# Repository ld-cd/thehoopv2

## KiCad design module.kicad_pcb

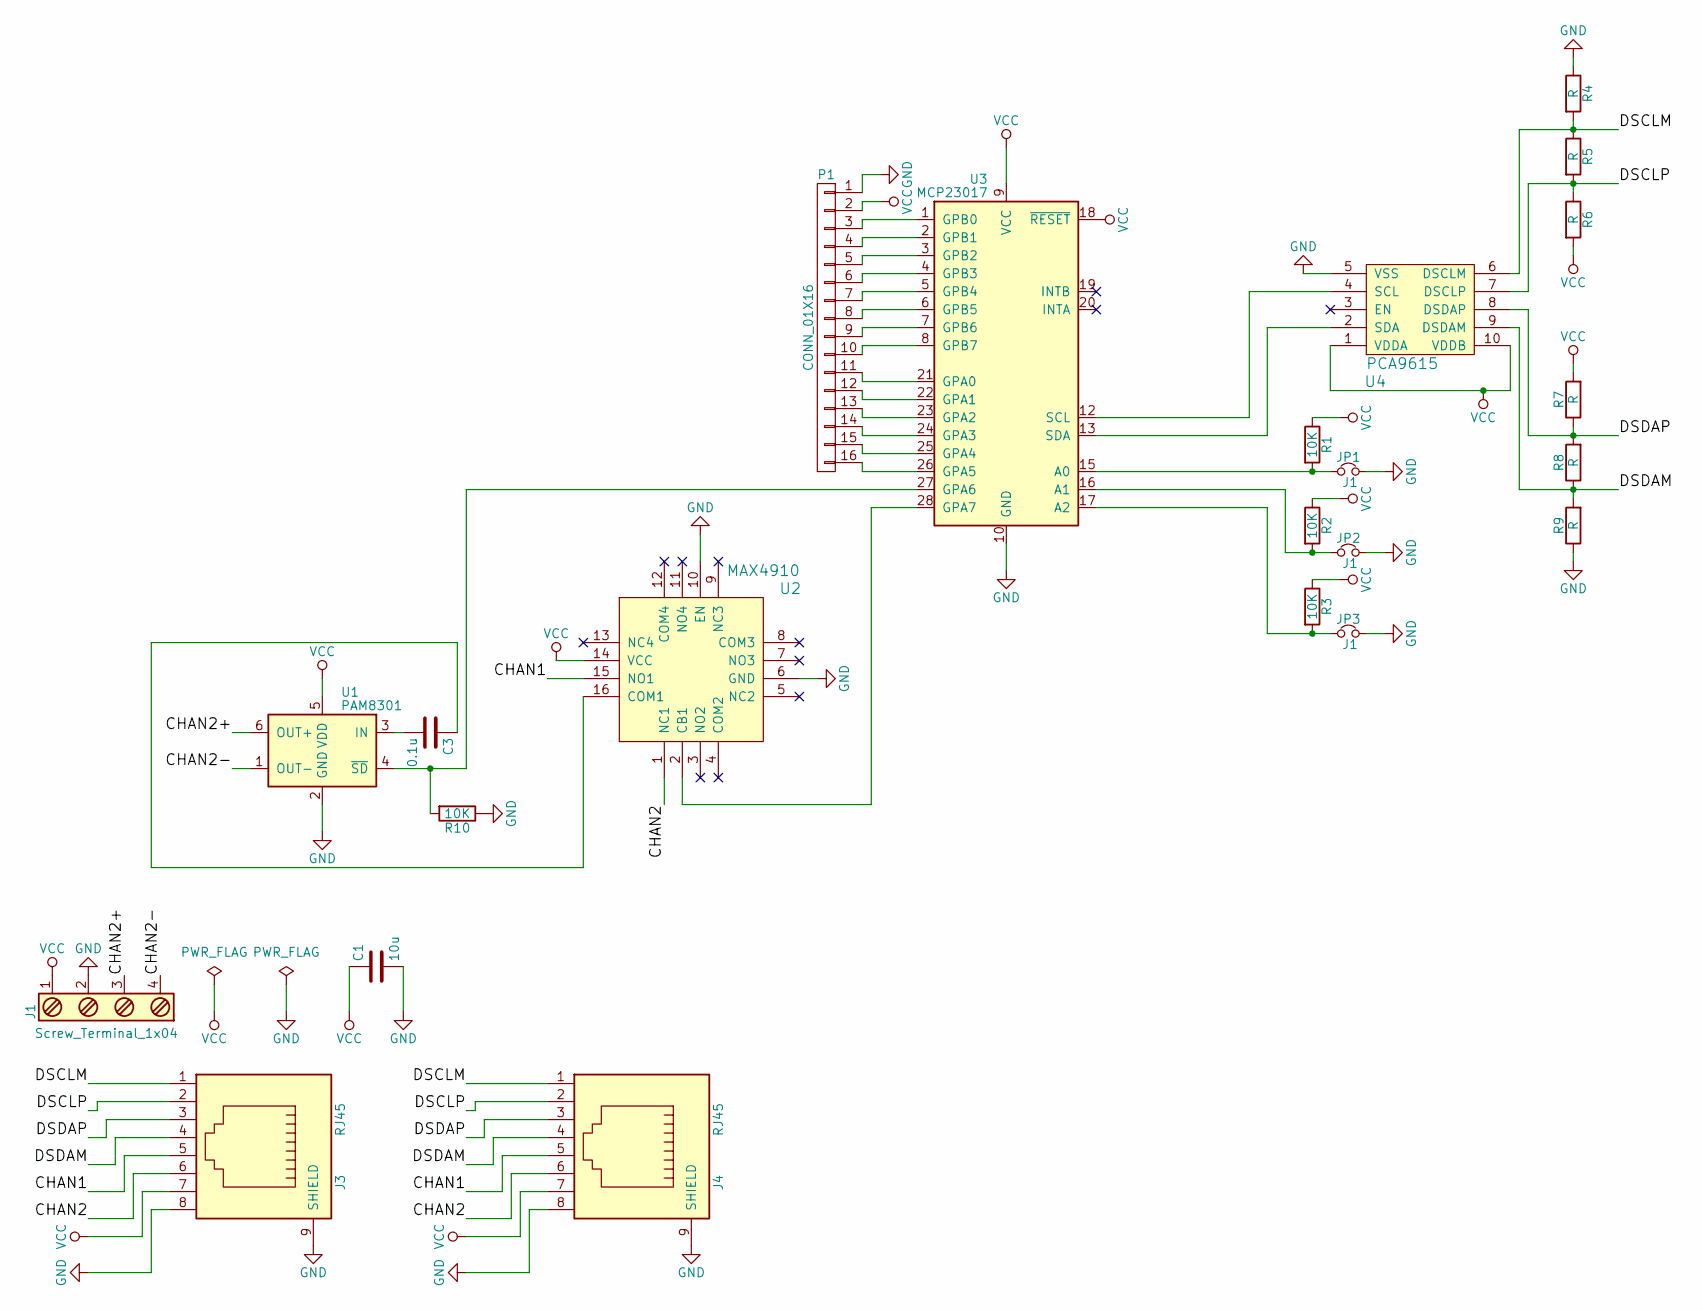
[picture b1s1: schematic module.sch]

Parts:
C1: 10u; C_0603
C3: 0.1u; C_0603
J1: Screw_Terminal_1x04; TerminalBlock_Pheonix_MKDS1.5-4pol
J3, J4: RJ45; rj45-8z4
JP1, JP2, JP3: J1; R_0603
P1: CONN_01X16; IDC_Header_Straight_16pins
R1, R2, R3, R10: 10K; R_0603
R4, R5, R6, R7, R8, R9: R; R_0603
U1: PAM8301; SOT-23-6
U2: MAX4910; QFN-16-1EP_3x3mm_Pitch0.5mm
U3: MCP23017; SSOP-28_5.3x10.2mm_Pitch0.65mm
U4: PCA9615; TSSOP-10_3x3mm_Pitch0.5mm

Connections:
/CHAN1: J3.5, J4.5, U2.15 (NO1)
/CHAN2: J3.6, J4.6, U2.1 (NC1)
/CHAN2+: J1.3, U1.6 (OUT+)
/CHAN2-: J1.4, U1.1 (OUT-)
/DSCLM: J3.1, J4.1, R4.2, R5.1, U4.6 (DSCLM)
/DSCLP: J3.2, J4.2, R5.2, R6.1, U4.7 (DSCLP)
/DSDAM: J3.4, J4.4, R8.1, R9.2, U4.9 (DSDAM)
/DSDAP: J3.3, J4.3, R7.1, R8.2, U4.8 (DSDAP)
GND: C1.2, J1.2, J3.8, J3.9 (SHIELD), J4.8, J4.9 (SHIELD), JP1.2, JP2.2, JP3.2, P1.1, R4.1, R9.1, R10.1, U1.2 (GND), U2.6 (GND), U2.10 (EN), U3.10 (GND), U4.5 (VSS)
unnamed: C3.1, U2.16 (COM1)
unnamed: C3.2, U1.3 (IN)
unnamed: JP1.1, R1.2, U3.15 (A0)
unnamed: JP2.1, R2.2, U3.16 (A1)
unnamed: JP3.1, R3.2, U3.17 (A2)
unnamed: P1.3, U3.1 (GPB0)
unnamed: P1.4, U3.2 (GPB1)
unnamed: P1.5, U3.3 (GPB2)
unnamed: P1.6, U3.4 (GPB3)
unnamed: P1.7, U3.5 (GPB4)
unnamed: P1.8, U3.6 (GPB5)
unnamed: P1.9, U3.7 (GPB6)
unnamed: P1.10, U3.8 (GPB7)
unnamed: P1.11, U3.21 (GPA0)
unnamed: P1.12, U3.22 (GPA1)
unnamed: P1.13, U3.23 (GPA2)
unnamed: P1.14, U3.24 (GPA3)
unnamed: P1.15, U3.25 (GPA4)
unnamed: P1.16, U3.26 (GPA5)
unnamed: R10.2, U1.4 (~SD), U3.27 (GPA6)
unnamed: U2.2 (CB1), U3.28 (GPA7)
unnamed: U3.12 (SCL), U4.4 (SCL)
unnamed: U3.13 (SDA), U4.2 (SDA)
VCC: C1.1, J1.1, J3.7, J4.7, P1.2, R1.1, R2.1, R3.1, R6.2, R7.2, U1.5 (VDD), U2.14 (VCC), U3.9 (VCC), U3.18 (~RESET), U4.1 (VDDA), U4.10 (VDDB)

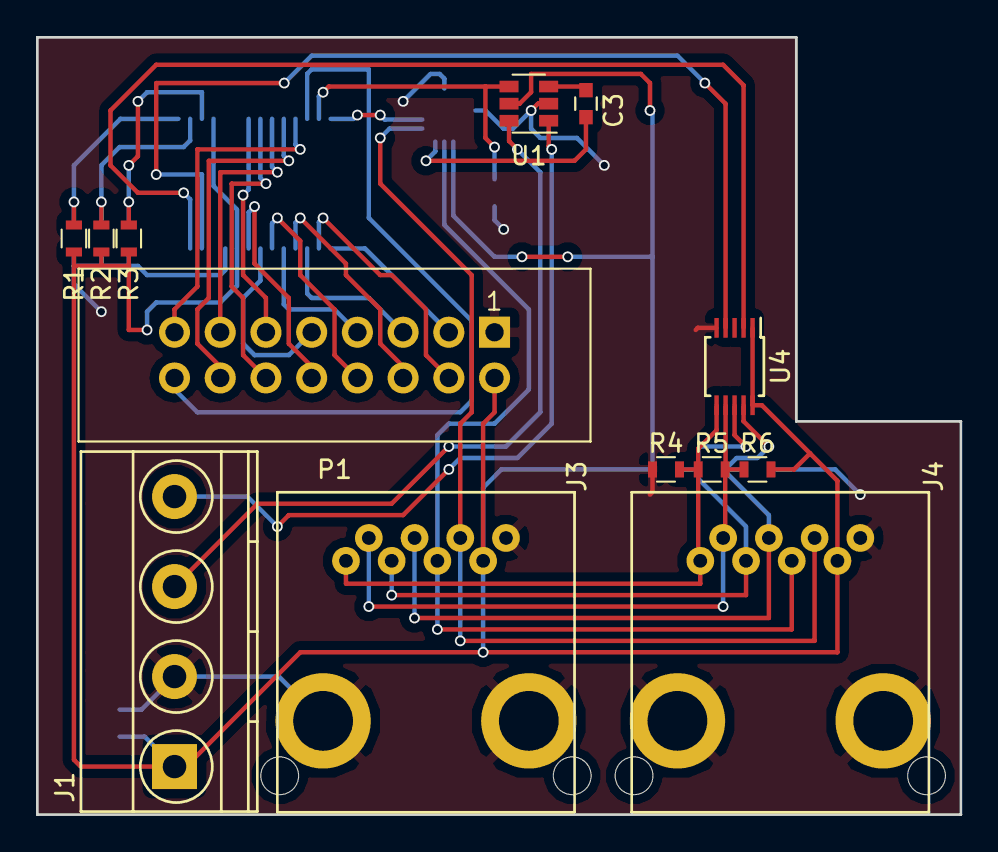
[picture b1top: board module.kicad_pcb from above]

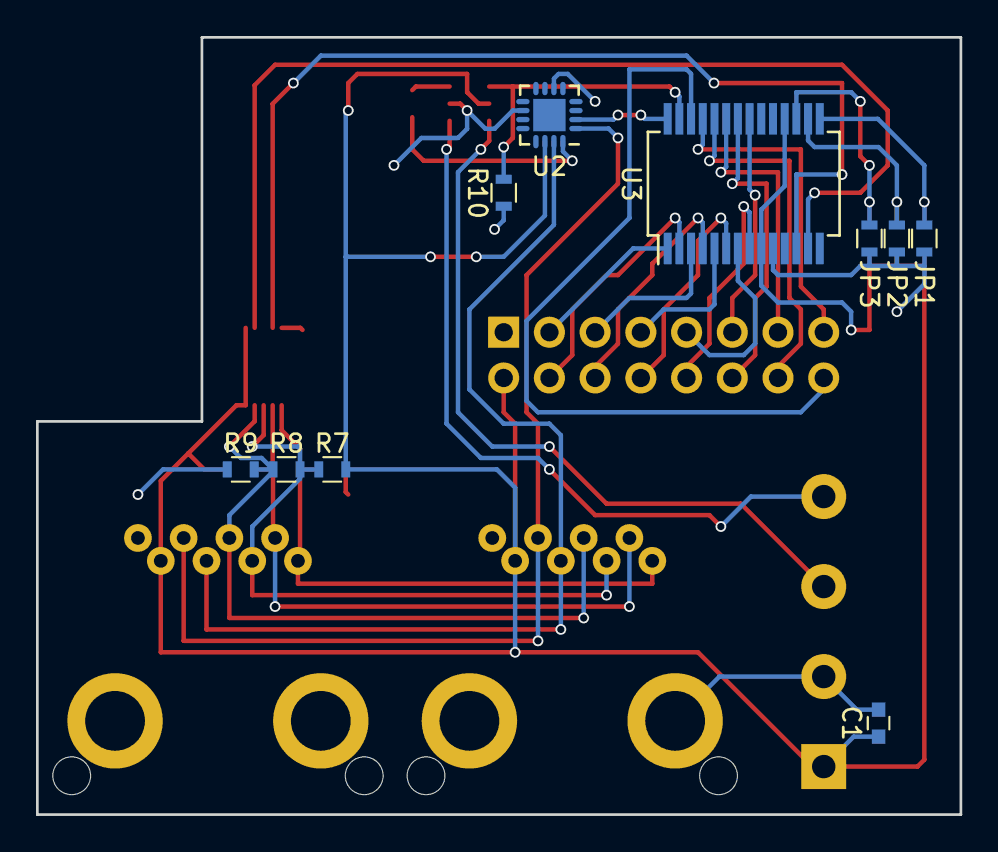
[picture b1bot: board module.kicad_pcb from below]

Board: 2 copper layers, 51.3 x 43.2 mm, 23 parts (10 on the bottom side), 33 nets.

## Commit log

2017-12-29 add bad readme
